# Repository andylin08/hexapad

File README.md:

# Macropad
---

# Bill of Materials (BOM)

| Component | Qty | Link |
|-----------|-----|------|
| SK6812-MINI RGB LED | 4 |
| Switching Diode (e.g., 1N4148) | 6 |
| 10 kΩ Trimmer Potentiometer | 1 | [https://www.switchelectronics.co.uk/products/10k-3296-variable-potentiometer-trimmer?variant=45366121595189&_gsid=a7fdeEfvG3t] |
| Cherry MX Key Switch | 6 |
| Rotary Encoder | 1 |
| Seeed XIAO-RP2040 Board | 1 |

---

## 📸 Images

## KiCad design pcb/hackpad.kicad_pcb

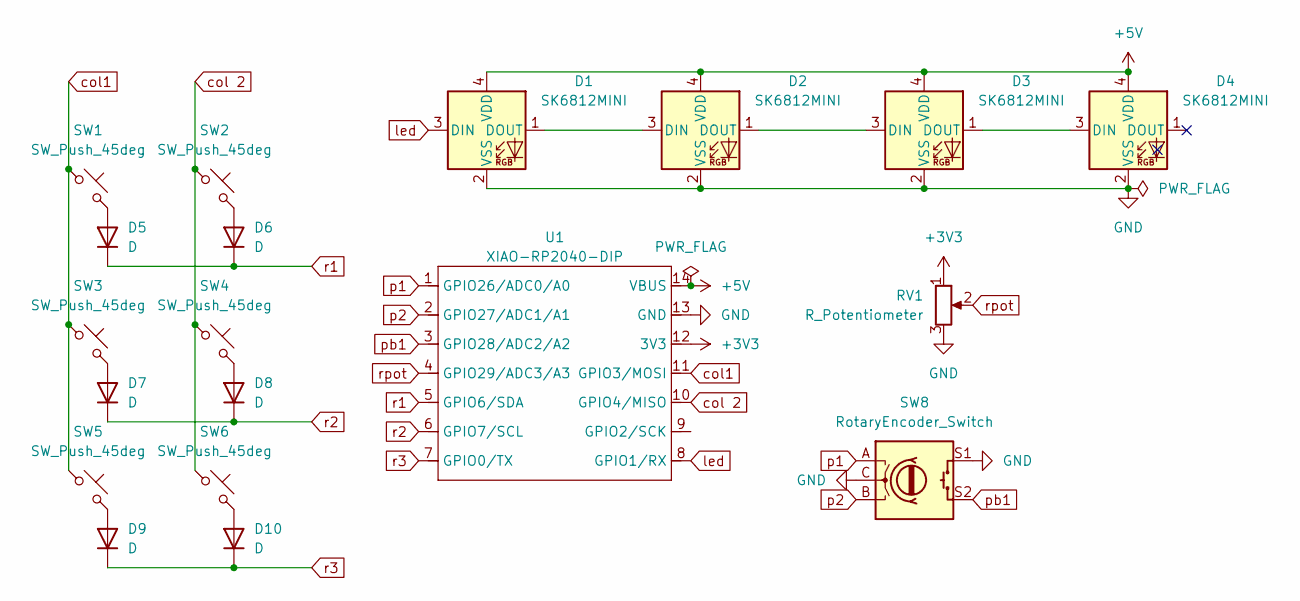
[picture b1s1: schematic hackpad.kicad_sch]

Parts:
D1, D2, D3, D4: SK6812MINI; LED_SK6812MINI_PLCC4_3.5x3.5mm_P1.75mm
D5, D6, D7, D8, D9, D10: D; D_SOD-123
RV1: R_Potentiometer; Potentiometer_Bourns_3266X_Horizontal
SW1, SW2, SW3, SW4, SW5, SW6: SW_Push_45deg; SW_Cherry_MX_1.00u_PCB
SW8: RotaryEncoder_Switch; RotaryEncoder_Alps_EC11E-Switch_Vertical_H20mm
U1: XIAO-RP2040-DIP

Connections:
+3V3: RV1.1, U1.12 (3V3)
+5V: D1.4 (VDD), D2.4 (VDD), D3.4 (VDD), D4.4 (VDD), U1.14 (VBUS)
GND: D1.2 (VSS), D2.2 (VSS), D3.2 (VSS), D4.2 (VSS), RV1.3, SW8.C, SW8.S1, U1.13 (GND)
unnamed: D1.1 (DOUT), D2.3 (DIN)
unnamed: D2.1 (DOUT), D3.3 (DIN)
unnamed: D3.1 (DOUT), D4.3 (DIN)
unnamed: D5.2 (A), SW1.2
unnamed: D6.2 (A), SW2.2
unnamed: D7.2 (A), SW3.2
unnamed: D8.2 (A), SW4.2
unnamed: D9.2 (A), SW5.2
unnamed: D10.2 (A), SW6.2
col1: SW1.1, SW3.1, SW5.1, U1.11 (GPIO3/MOSI)
col 2: SW2.1, SW4.1, SW6.1, U1.10 (GPIO4/MISO)
led: D1.3 (DIN), U1.8 (GPIO1/RX)
p1: SW8.A, U1.1 (GPIO26/ADC0/A0)
p2: SW8.B, U1.2 (GPIO27/ADC1/A1)
pb1: SW8.S2, U1.3 (GPIO28/ADC2/A2)
r1: D5.1 (K), D6.1 (K), U1.5 (GPIO6/SDA)
r2: D7.1 (K), D8.1 (K), U1.6 (GPIO7/SCL)
r3: D9.1 (K), D10.1 (K), U1.7 (GPIO0/TX)
rpot: RV1.2, U1.4 (GPIO29/ADC3/A3)

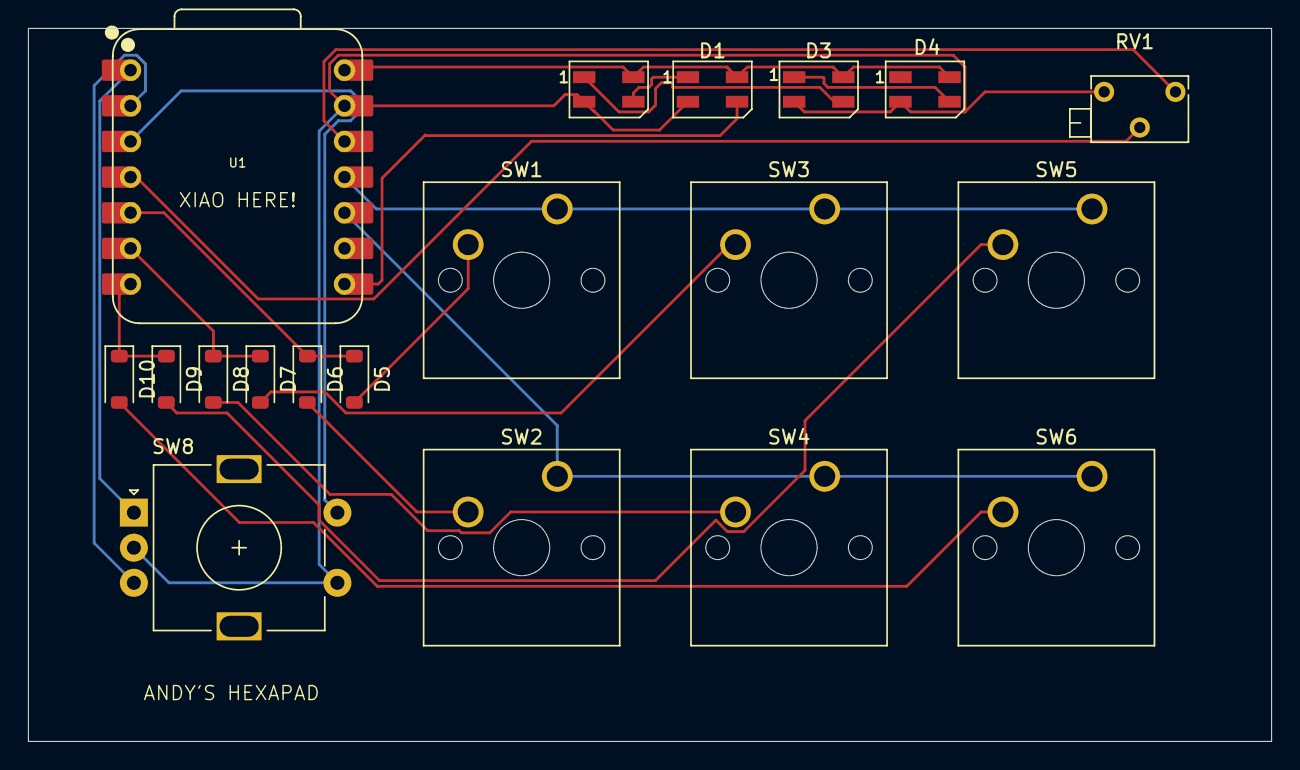
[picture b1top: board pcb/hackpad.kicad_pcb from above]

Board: 2 copper layers, 88.6 x 50.8 mm, 19 parts (0 on the bottom side), 22 nets.

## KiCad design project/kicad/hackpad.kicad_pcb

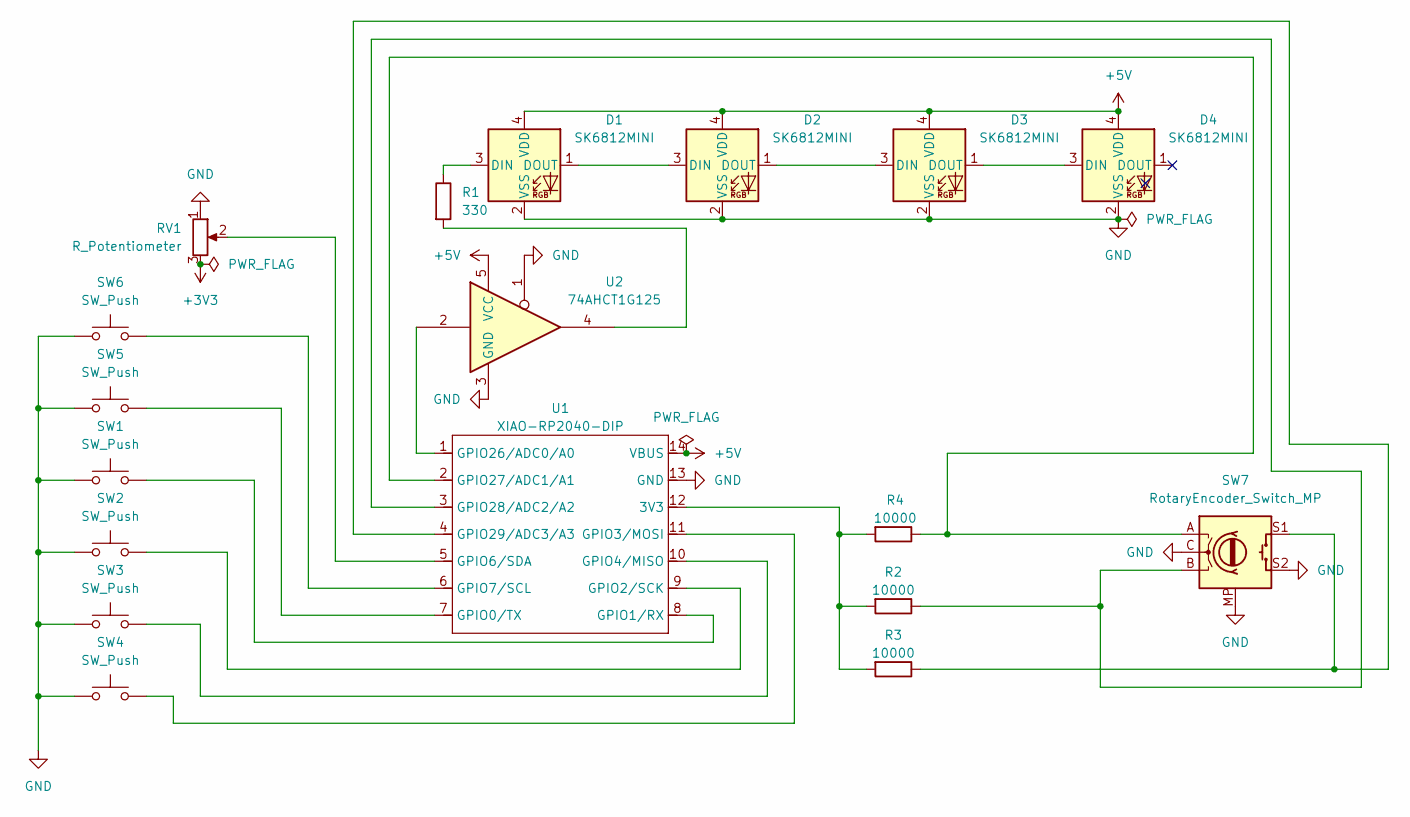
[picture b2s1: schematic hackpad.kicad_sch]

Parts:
D1, D2, D3, D4: SK6812MINI; LED_SK6812MINI_PLCC4_3.5x3.5mm_P1.75mm
R1: 330; R_0805_2012Metric_Pad1.20x1.40mm_HandSolder
R2, R3, R4: 10000; R_0805_2012Metric_Pad1.20x1.40mm_HandSolder
RV1: R_Potentiometer; Potentiometer_Bourns_3296W_Vertical
SW1, SW2, SW3, SW4, SW5, SW6: SW_Push; SW_Cherry_MX_1.00u_PCB
SW7: RotaryEncoder_Switch_MP; RotaryEncoder_Alps_EC11E-Switch_Vertical_H20mm
U1: XIAO-RP2040-DIP
U2: 74AHCT1G125; SOT-23-5_HandSoldering

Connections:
+3V3: RV1.3
+5V: D1.4 (VDD), D2.4 (VDD), D3.4 (VDD), D4.4 (VDD), U1.14 (VBUS), U2.5 (VCC)
GND: D1.2 (VSS), D2.2 (VSS), D3.2 (VSS), D4.2 (VSS), RV1.1, SW1.1, SW2.1, SW3.1, SW4.1, SW5.1, SW6.1, SW7.C, SW7.MP, SW7.S2, U1.13 (GND), U2.1, U2.3 (GND)
unnamed: D1.3 (DIN), R1.1
unnamed: D1.1 (DOUT), D2.3 (DIN)
unnamed: D2.1 (DOUT), D3.3 (DIN)
unnamed: D3.1 (DOUT), D4.3 (DIN)
unnamed: R1.2, U2.4
unnamed: R2.2, R3.2, R4.2, U1.12 (3V3)
unnamed: SW5.2, U1.7 (GPIO0/TX)
unnamed: SW1.2, U1.8 (GPIO1/RX)
unnamed: SW2.2, U1.9 (GPIO2/SCK)
unnamed: SW4.2, U1.11 (GPIO3/MOSI)
unnamed: SW3.2, U1.10 (GPIO4/MISO)
unnamed: RV1.2, U1.5 (GPIO6/SDA)
unnamed: SW6.2, U1.6 (GPIO7/SCL)
unnamed: U1.1 (GPIO26/ADC0/A0), U2.2
unnamed: R4.1, SW7.A, U1.2 (GPIO27/ADC1/A1)
unnamed: R2.1, SW7.B, U1.3 (GPIO28/ADC2/A2)
unnamed: R3.1, SW7.S1, U1.4 (GPIO29/ADC3/A3)

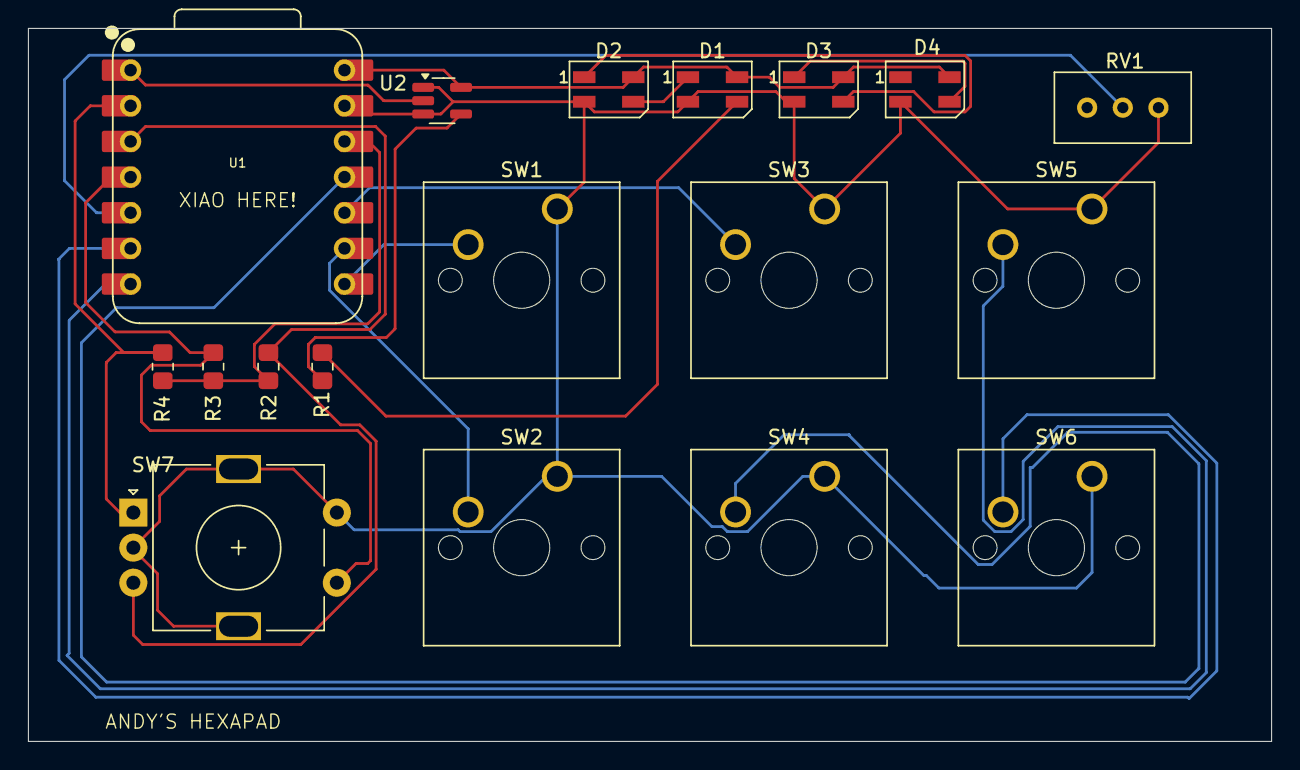
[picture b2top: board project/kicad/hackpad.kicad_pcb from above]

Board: 2 copper layers, 88.6 x 50.8 mm, 18 parts (0 on the bottom side), 19 nets.
